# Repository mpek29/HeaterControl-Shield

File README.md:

# HeaterControl-Shield

## 🚀 Overview

**HeaterControl-Shield** is an open-source electronic board designed to control a **heating resistor**, measure the **consumed current**, and detect the **temperature** near the heating resistor. This board is shaped as an **Arduino shield** and optimized for use with an **STM32 Nucleo**.

## 🎯 Main Features
- 🔥 **Heating resistor control** via an **N-channel MOSFET**.
- ⚡ **Current consumption measurement** using a **shunt resistor** and an **operational amplifier**.
- 🌡️ **Temperature sensing** using a **thermistor** integrated into a **Wheatstone bridge**, amplified by an **instrumentation amplifier**.
- 🛠️ **Open-source and customizable design** to adapt to specific project needs.

## 📝 Technical Specifications
| 🏷️ Feature | 🔍 Description |
|----------------|-------------|
| 🔌 **Power Input** | 5V - 12V |
| 🔥 **Heating Control** | N-channel MOSFET for power control |
| ⚡ **Current Measurement** | Shunt resistor + Operational amplifier |
| 🌡️ **Temperature Sensing** | Wheatstone bridge + Instrumentation amplifier |
| 🔄 **Interface** | Compatible with **Arduino Shield** and **STM32 Nucleo** |
| 🖥️ **PCB Design** | Open-source & customizable |
| 🌍 **Applications** | Thermal control projects, embedded systems, temperature regulation |

## 📐 PCB Preview
| 📜 Schematic | 🖥️ PCB Layout | 🏗️ 3D View |
|-----------|-----------|-----------|
|  |  |  |

## 🔗 Main Connections
| Pin | Function |
|-----|---------|
| VIN | Main power input |
| GND | Ground |
| HEAT_CTRL | PWM signal to activate heating |
| CURR_SENSE | Amplified output of current measurement |
| TEMP_SENSE | Amplified output of temperature measurement |

## 🌟 License
This project is open-source. Feel free to use, modify, and contribute! 🚀

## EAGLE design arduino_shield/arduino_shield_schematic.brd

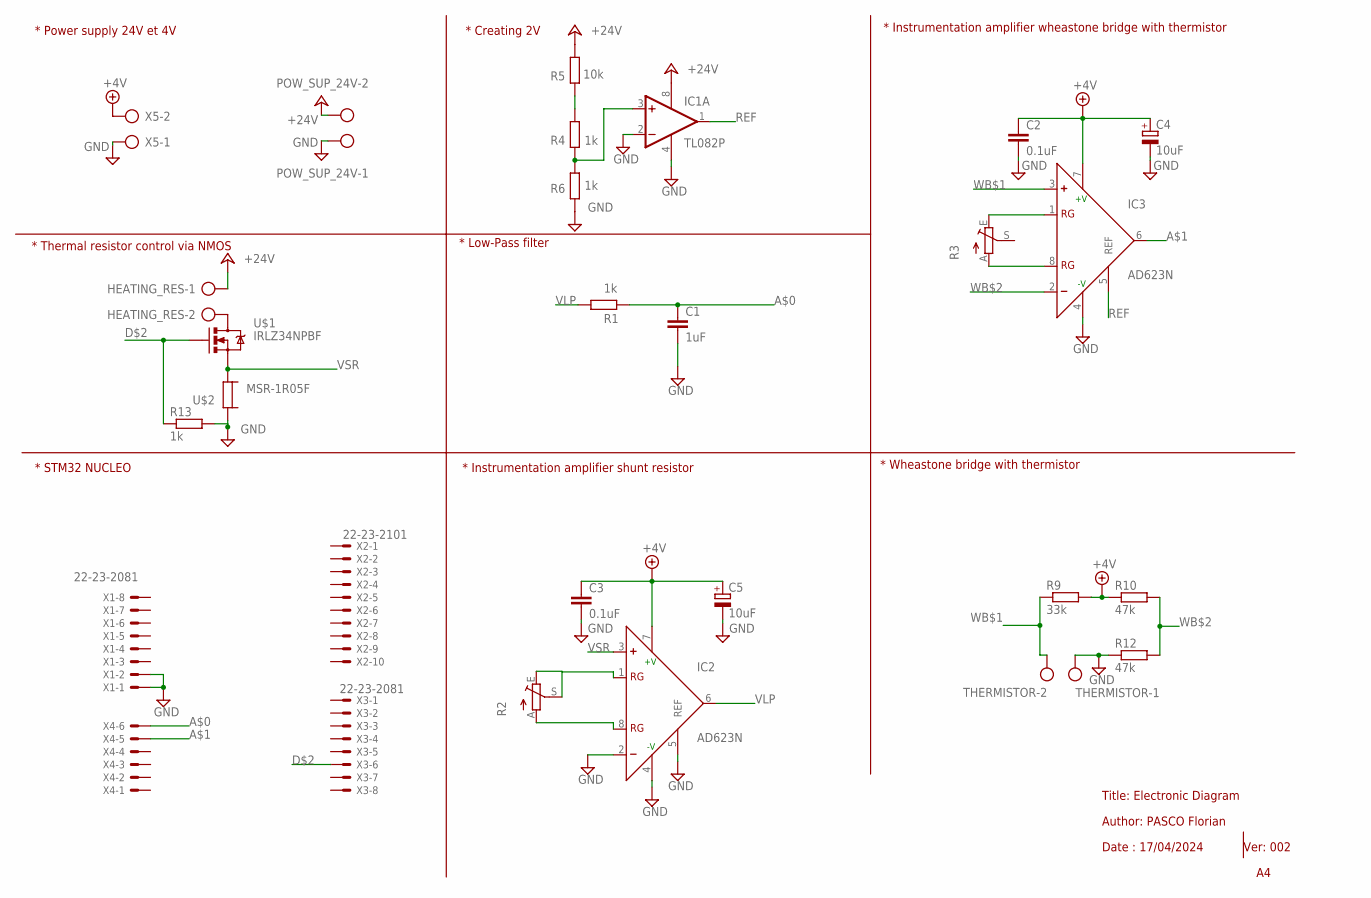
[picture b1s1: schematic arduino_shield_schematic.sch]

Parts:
C1: 1uF; C025-025X050
C2, C3: 0.1uF; C025-025X050
C4, C5: 10uF; E2,5-6E
HEATING_RES: AK300/2
IC1: TL082P; DIL08
IC2, IC3: AD623N; DIL08
POW_SUP_24V: AK300/2
R1, R4, R6, R13: 1k; 0207/10
R2, R3: TRIM_EU-S64W; S64W
R5: 10k; 0207/10
R9: 33k; 0207/10
R10, R12: 47k; 0207/10
THERMISTOR: AK300/2
U$1: IRLZ34NPBF; TO-220(2)
U$2: MSR-1R05F; MSR1
X1, X3: 22-23-2081
X2: 22-23-2101
X4: 22-23-2061
X5: AK300/2

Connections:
+4.1V: C2.1, C3.1, C4.+, C5.+, IC2.7 (+V), IC3.7 (+V), R9.2, R10.1, X5.2
+24V: HEATING_RES.1, IC1.8 (V+), POW_SUP_24V.2, R5.2
A$0: C1.1, R1.1, X4.6
A$1: IC3.6 (OUT), X4.5
D$2: R13.1, U$1.IN (G), X3.6
GND: C1.2, C2.2, C3.2, C4.-, C5.-, IC1.2 (-IN), IC1.4 (V-), IC2.2 (-), IC2.4 (-V), IC2.5 (REF), IC3.4 (-V), POW_SUP_24V.1, R6.1, R12.1, R13.2, THERMISTOR.1, U$2.P$2 (2), X1.1, X1.2, X5.1
unnamed: R2.E, R2.S
unnamed: R4.2, R5.1
unnamed: IC1.3 (+IN), R4.1, R6.2
unnamed: IC2.8 (RG), R2.A
unnamed: IC3.1 (RG), R3.E
unnamed: IC3.8 (RG), R3.A
unnamed: HEATING_RES.2, U$1.GND (D)
REF: IC1.1 (OUT), IC3.5 (REF)
VLP: IC2.6 (OUT), R1.2
VSR: IC2.3 (+), U$1.OUT (S), U$2.P$1 (1)
WB$1: IC3.3 (+), R9.1, THERMISTOR.2
WB$2: IC3.2 (-), R10.2, R12.2

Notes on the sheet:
Title: Electronic Diagram
Author: PASCO Florian
* STM32 NUCLEO
* Power supply 24V et 4V
* Creating 2V
* Thermal resistor control via NMOS
* Instrumentation amplifier shunt resistor
* Instrumentation amplifier wheastone bridge with thermistor
* Wheastone bridge with thermistor
* Low-Pass filter
Ver: 002
Date : 17/04/2024

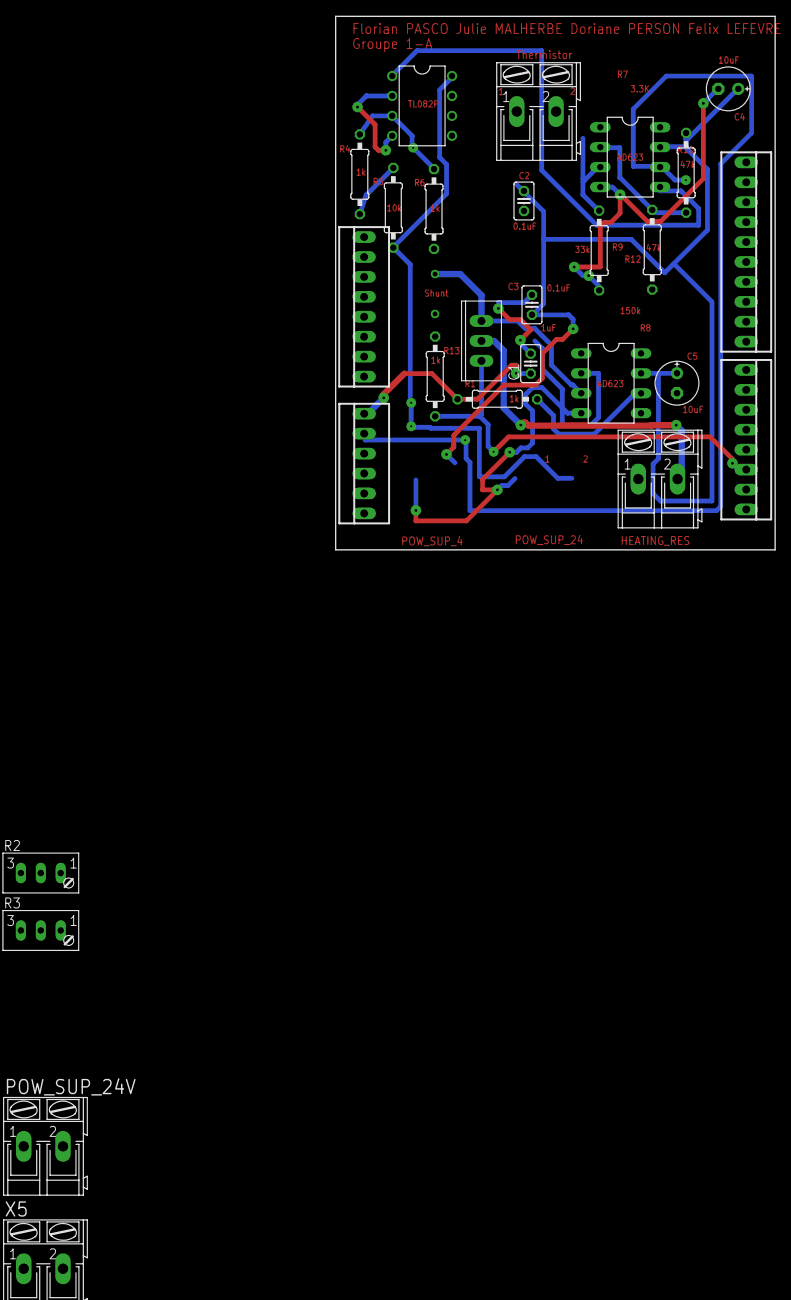
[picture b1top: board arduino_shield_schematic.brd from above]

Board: 2 copper layers, 56.0 x 68.0 mm, 28 parts (0 on the bottom side), 18 nets.

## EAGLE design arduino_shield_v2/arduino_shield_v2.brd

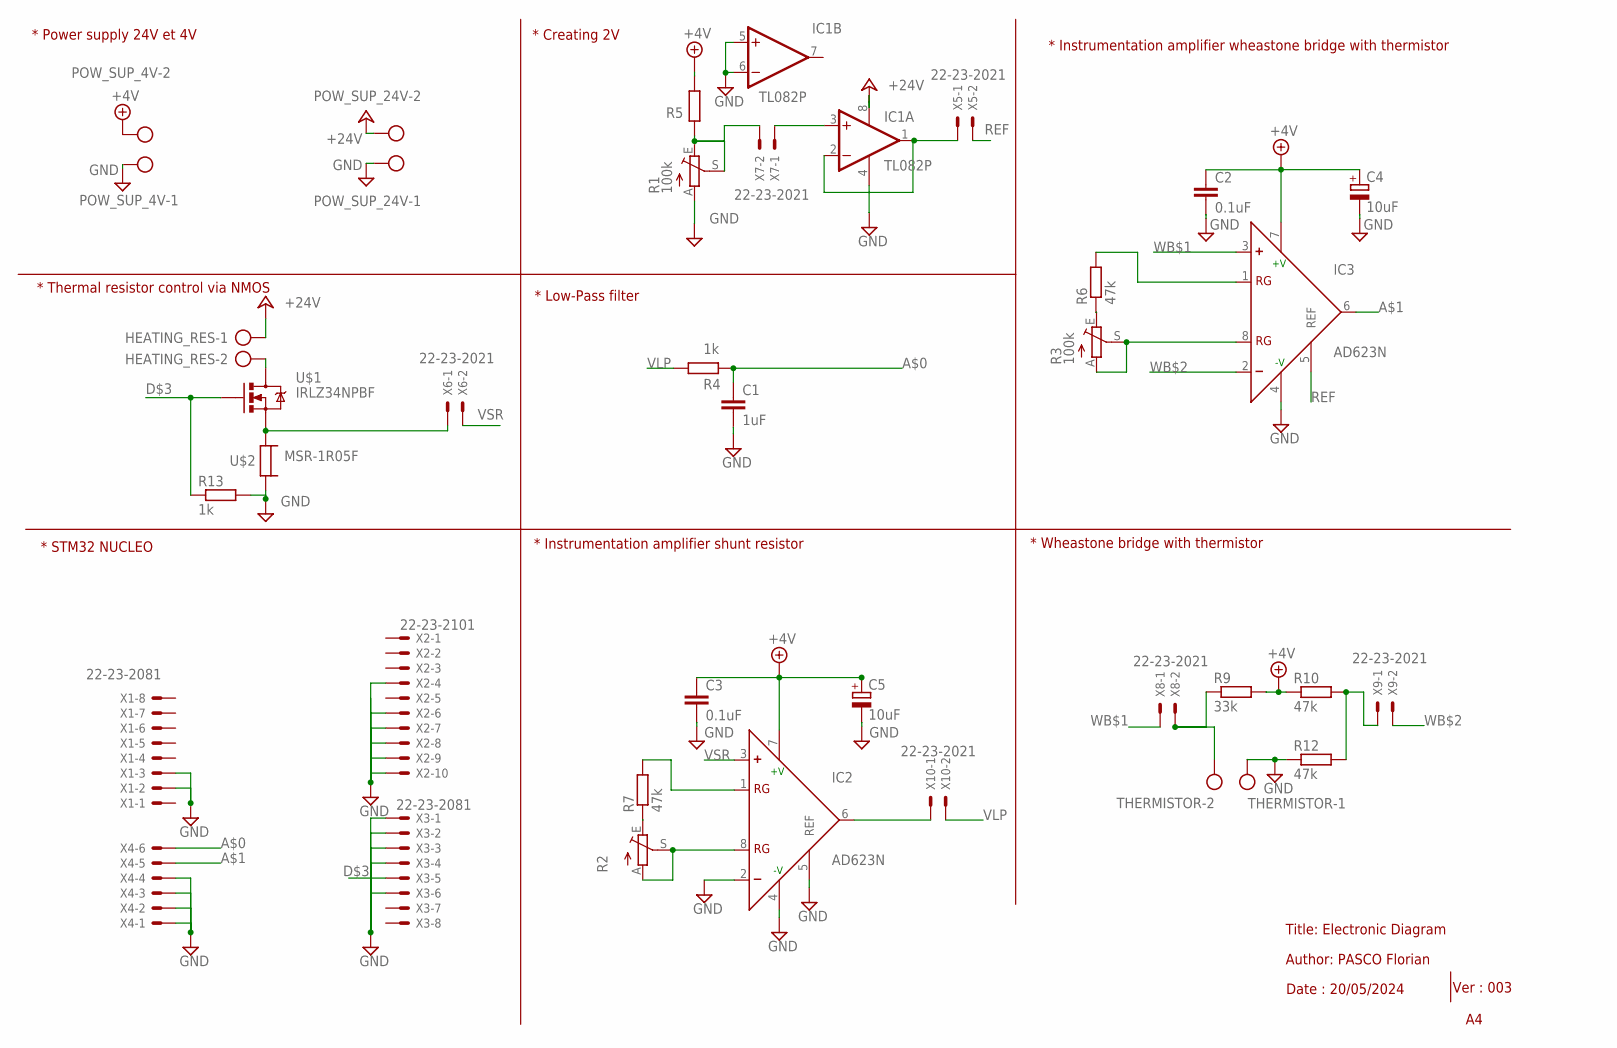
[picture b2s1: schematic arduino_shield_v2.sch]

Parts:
C1: 1uF; C050-025X075
C2, C3: 0.1uF; C050-025X075
C4, C5: 10uF; E5-5
HEATING_RES: AK300/2
IC1: TL082P; DIL08
IC2, IC3: AD623N; DIL08
POW_SUP_4V, POW_SUP_24V: AK300/2
R1, R3: 100k; S64W
R2: TRIM_EU-S64W; S64W
R4, R13: 1k; 0207/10
R5, R6, R7, R10, R12: 47k; 0207/10
R9: 33k; 0207/10
THERMISTOR: AK300/2
U$1: IRLZ34NPBF; TO-220(2)
U$2: MSR-1R05F; MSR1
X1, X3: 22-23-2081
X2: 22-23-2101
X4: 22-23-2061
X5, X6, X7, X8, X9, X10: 22-23-2021

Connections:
+4.1V: C2.1, C3.1, C4.+, C5.+, IC2.7 (+V), IC3.7 (+V), POW_SUP_4V.2, R5.2, R9.2, R10.1
+24V: HEATING_RES.1, IC1.8 (V+), POW_SUP_24V.2
A$0: C1.1, R4.1, X4.6
A$1: IC3.6 (OUT), X4.5
D$3: R13.1, U$1.IN (G), X3.5
GND: C1.2, C2.2, C3.2, C4.-, C5.-, IC1.4 (V-), IC1.5 (+IN), IC1.6 (-IN), IC2.2 (-), IC2.4 (-V), IC2.5 (REF), IC3.4 (-V), POW_SUP_4V.1, POW_SUP_24V.1, R1.A, R12.1, R13.2, THERMISTOR.1, U$2.P$2 (2), X1.2, X1.3, X2.4, X2.6, X2.7, X2.8, X2.9, X2.10, X3.1, X3.2, X3.3, X3.4, X3.6, X4.1, X4.2, X4.3, X4.4
unnamed: R1.E, R1.S, R5.1, X7.2
unnamed: R2.E, R7.1
unnamed: IC3.1 (RG), R6.2
unnamed: IC3.8 (RG), R3.A, R3.S
unnamed: IC2.8 (RG), R2.A, R2.S
unnamed: R3.E, R6.1
unnamed: IC2.1 (RG), R7.2
unnamed: IC1.3 (+IN), X7.1
unnamed: IC2.6 (OUT), X10.1
unnamed: HEATING_RES.2, U$1.GND (D)
unnamed: R10.2, R12.2, X9.1
unnamed: R9.1, THERMISTOR.2, X8.2
unnamed: IC1.1 (OUT), IC1.2 (-IN), X5.1
unnamed: U$1.OUT (S), U$2.P$1 (1), X6.1
REF: IC3.5 (REF), X5.2
VLP: R4.2, X10.2
VSR: IC2.3 (+), X6.2
WB$1: IC3.3 (+), X8.1
WB$2: IC3.2 (-), X9.2

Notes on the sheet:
Title: Electronic Diagram
Author: PASCO Florian
* STM32 NUCLEO
Date : 20/05/2024
Ver : 003
* Instrumentation amplifier wheastone bridge with thermistor
* Creating 2V
* Power supply 24V et 4V
* Wheastone bridge with thermistor
* Thermal resistor control via NMOS
* Instrumentation amplifier shunt resistor
* Low-Pass filter

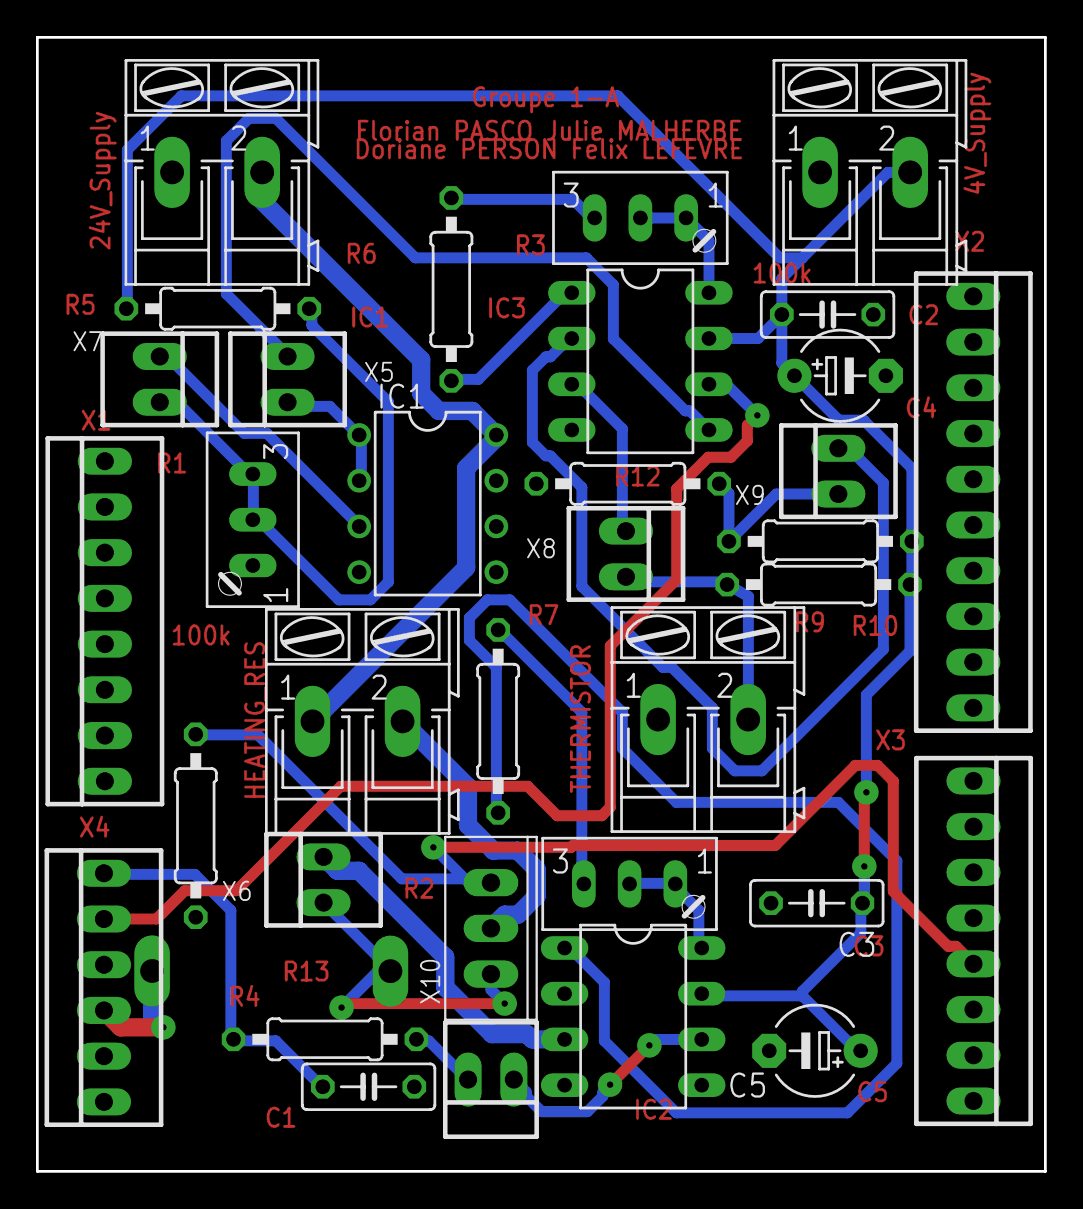
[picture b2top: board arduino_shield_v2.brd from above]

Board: 2 copper layers, 56.0 x 63.0 mm, 35 parts (0 on the bottom side), 25 nets.
